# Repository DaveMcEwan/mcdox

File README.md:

mcdox - Mechanical Computer Keyboard
====================================

Layout is similar to than of the Ergodox project, but in a unibody case.

Subdirectories
--------------

- case - Lasercut design produced by exporting SVGs from KiCAD.
- doc - Documents like datasheets stored for handy reference.
- keycap - STL model generator written in OpenSCAD suitable for FDM printing.
  Generated models are tracked in `keycap/stl` because it takes a while (~10
  minutes) to generate them.
- pcb/ctrl - TODO Breakout PCB for connecting controller to switch grids.
- pcb/hand - Reversible PCB which connects the switches in a grid.
  - 38 buttons distributed over 5 rows, 8 columns.
  - Lengths beside mounting holes (6mm, 15mm, 25mm) are for standoffs to
    achieve a tenting.
  - Connect to control board with 15 core, 1mm pitch FFC-FPC cable.
    <https://www.te.com/usa-en/product-1-84953-5.html>
    <https://www.digikey.com/en/products/detail/te-connectivity-amp-connectors/1-84953-5/2567541>
    <https://uk.farnell.com/amp-te-connectivity/1-84953-5/connector-ffc-fpc-15pos-1rows/dp/3398659>
    <https://uk.farnell.com/multicomp-pro/mp-ffca10150503a/ffc-cord-15p-same-side-50mm-wht/dp/3385337>
    <https://uk.farnell.com/multicomp-pro/mp-ffca10151003a/ffc-cord-15p-same-side-100mm-wht/dp/3385339>
  - Low level lighting with LED on top and/or bottom, depending how the case
    looks.
  - All diodes (1N4148 compatible), LEDs, and resistors are 0603 (imperial).
- release - Stuff that's actually been manufactured.

BOM
---

- Keycaps - The functionally simplest parts which are also the most difficult to
  source.
  18x 1.5u, 56x 1u
- Case - Standard 3mm acrylic from laser cutter.
- PCBs - 1.2mm FR4, 2-layer, 0.15mm width/clearance
  2x mcdoxHand, 1x mcdoxCtrl
- Switches - CherryMX, or compatible like Gateron, Kailh.
  74x
- Diodes - 1 per switch.
  74x
- Microcontroller - Arduino Pro Micro from Sparkfun, or clone.
- FPC connectors
  4x
- FPC cables - Connect hand PCBs to central controller.
- LEDs - 0603 footprint
  2x
- Resistors - For LEDs and switch matrix.
  10x 220R 0603
- Pushbutton - For putting Arduino Pro Micro into programming mode.
  1x

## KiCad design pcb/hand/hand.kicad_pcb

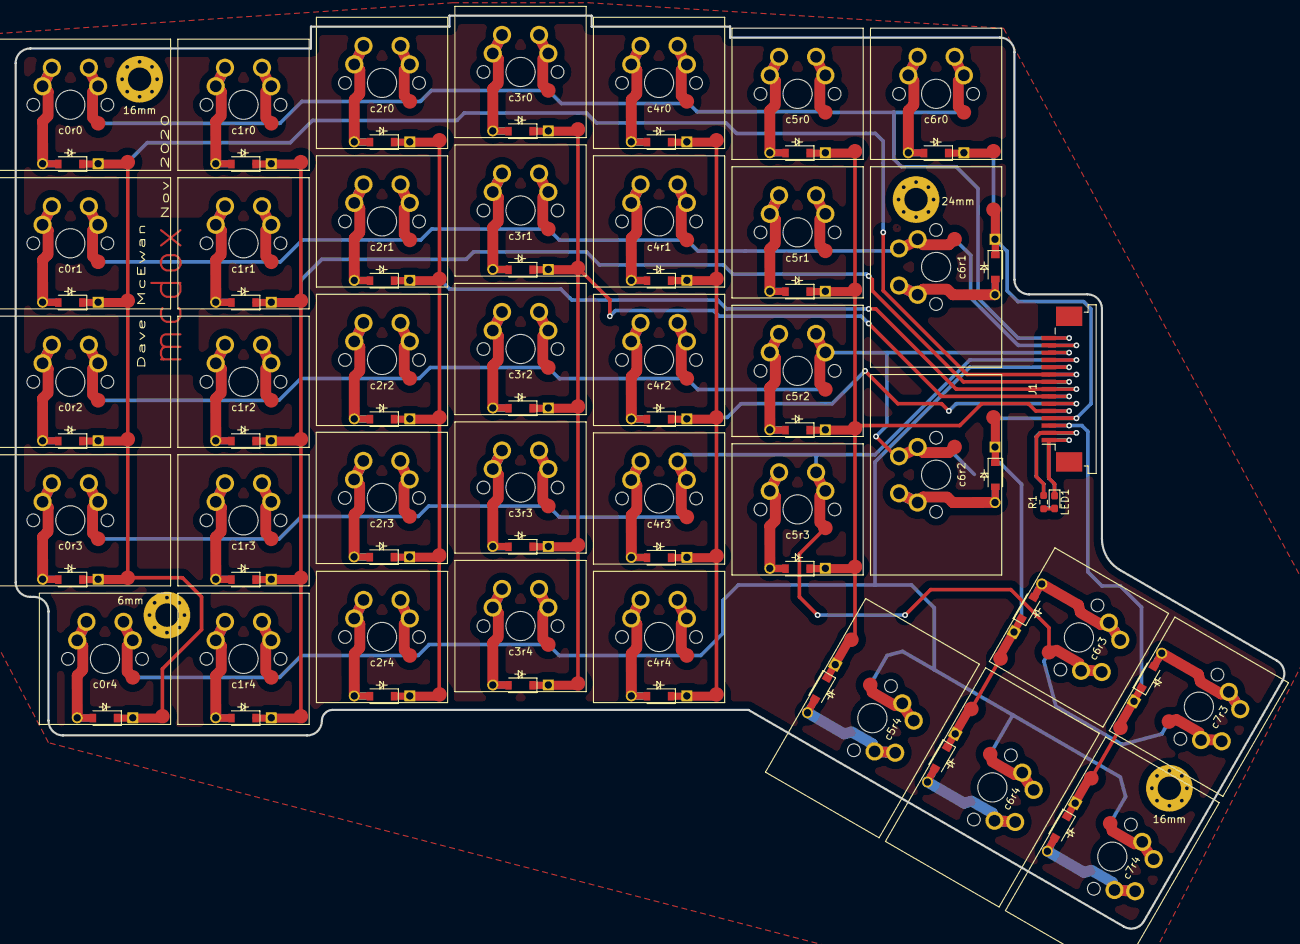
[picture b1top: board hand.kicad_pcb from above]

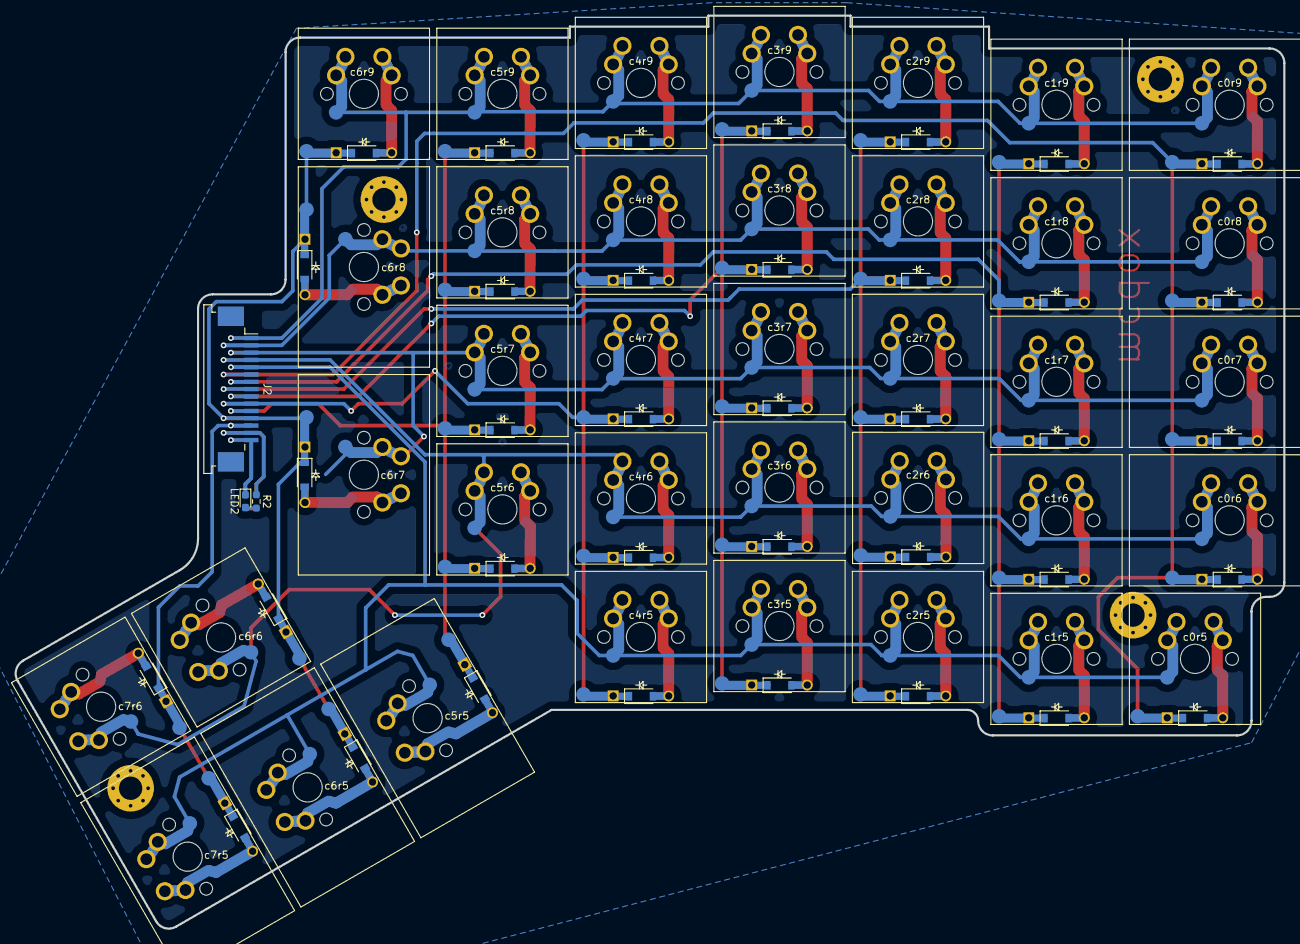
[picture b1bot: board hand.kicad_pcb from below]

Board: 2 copper layers, 174.0 x 125.2 mm, 47 parts (6 on the bottom side), 17 nets.

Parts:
6mm, 16mm, 16mm#2, 24mm: MountingHole_3.2mm_M3_Pad_Via
J1, J2: Conn_01x15; TE_1-84953-5_1x15-1MP_P1.0mm_Horizontal
LED1, LED2: LED; D_0603_1608Metric_Pad1.05x0.95mm_HandSolder
R1, R2: 100; R_0603_1608Metric_Pad0.98x0.95mm_HandSolder
c0r0, c0r1, c0r2, c0r3, c5r4, c6r1, c6r2, c6r4, c7r4: switchDiode; reversibleMX_15u
c0r4, c1r0, c1r1, c1r2, c1r3, c1r4, c2r0, c2r1, c2r2, c2r3, c2r4, c3r0, c3r1, c3r2, c3r3, c3r4, c4r0, c4r1, c4r2, c4r3, c4r4, c5r0, c5r1, c5r2, c5r3, c6r0, c6r3, c7r3: switchDiode; reversibleMX_10u

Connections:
+3V3: J1.2, J2.14, R1.1, R2.1
GND: J1.1, J2.15, LED1.1, LED2.1
unnamed: LED1.2, R1.2
unnamed: LED2.2, R2.2
col0: J1.10, J2.6, c0r0.2, c0r1.2, c0r2.2, c0r3.2, c0r4.2
col1: J1.9, J2.7, c1r0.2, c1r1.2, c1r2.2, c1r3.2, c1r4.2
col2: J1.8, J2.8, c2r0.2, c2r1.2, c2r2.2, c2r3.2, c2r4.2
col3: J1.7, J2.9, c3r0.2, c3r1.2, c3r2.2, c3r3.2, c3r4.2
col4: J1.6, J2.10, c4r0.2, c4r1.2, c4r2.2, c4r3.2, c4r4.2
col5: J1.5, J2.11, c5r0.2, c5r1.2, c5r2.2, c5r3.2, c5r4.2
col6: J1.4, J2.12, c6r0.2, c6r1.2, c6r2.2, c6r3.2, c6r4.2
col7: J1.3, J2.13, c7r3.2, c7r4.2
row0: J1.15, J2.1, c0r0.1, c1r0.1, c2r0.1, c3r0.1, c4r0.1, c5r0.1, c6r0.1
row1: J1.14, J2.2, c0r1.1, c1r1.1, c2r1.1, c3r1.1, c4r1.1, c5r1.1, c6r1.1
row2: J1.13, J2.3, c0r2.1, c1r2.1, c2r2.1, c3r2.1, c4r2.1, c5r2.1, c6r2.1
row3: J1.12, J2.4, c0r3.1, c1r3.1, c2r3.1, c3r3.1, c4r3.1, c5r3.1, c6r3.1, c7r3.1
row4: J1.11, J2.5, c0r4.1, c1r4.1, c2r4.1, c3r4.1, c4r4.1, c5r4.1, c6r4.1, c7r4.1

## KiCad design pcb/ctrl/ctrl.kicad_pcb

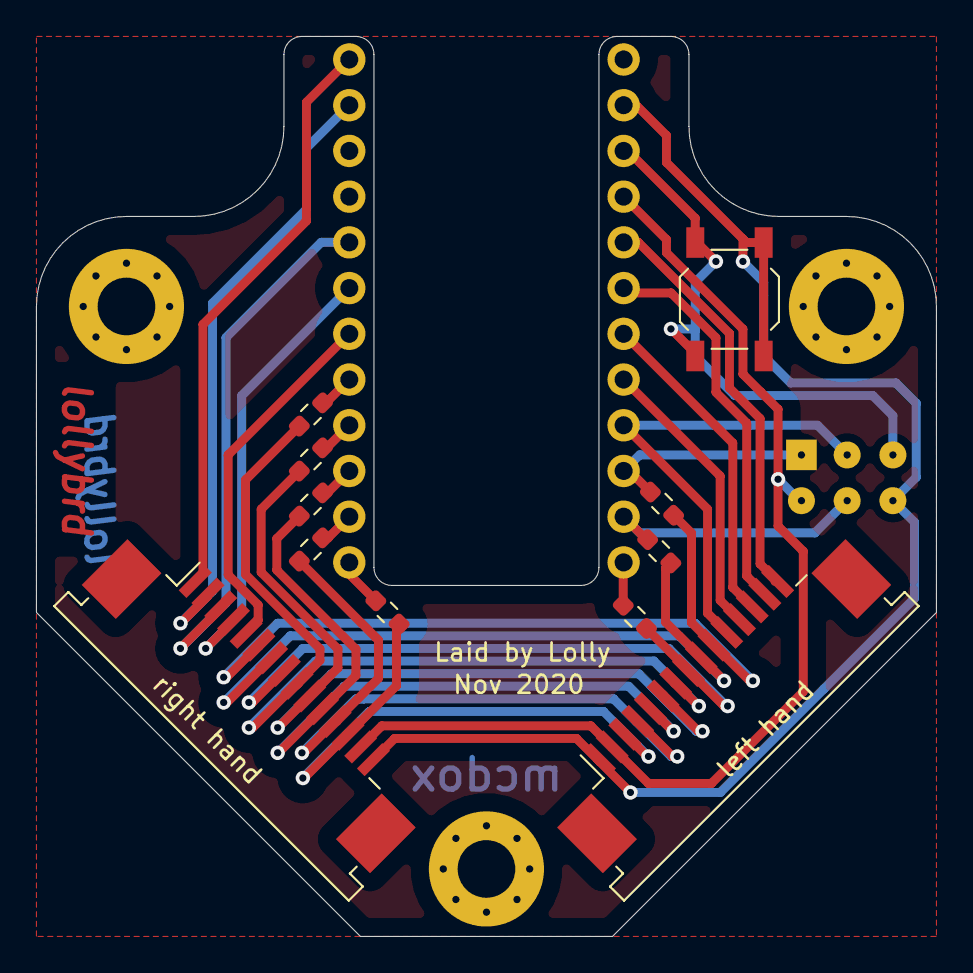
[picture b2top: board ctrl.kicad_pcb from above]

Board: 2 copper layers, 50.0 x 50.0 mm, 13 parts (1 on the bottom side), 29 nets.

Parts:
ICSP: Conn_02x03_Odd_Even; PinHeader_2x03_P2.54mm_Vertical
Jleft1: Conn_01x15; TE_1-84953-5_1x15-1MP_P1.0mm_Horizontal
Jright1: Conn_01x15; TE_1-84953-5_1x15-1MP_P1.0mm_Horizontal
R0, R1, R2, R3, R4, R5, R6, R7: 220; R_0603_1608Metric_Pad0.98x0.95mm_HandSolder
SW1: SW_Push; SW_SPST_TL3342
U1: ArduinoProMicro

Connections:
GND: ICSP.6, Jleft1.1, Jright1.15, SW1.2, U1.14
MISO: ICSP.1, R0.2, U1.22
MOSI: ICSP.4, R1.2, U1.23
unnamed: R2.2, U1.24
unnamed: R3.2, U1.12
unnamed: R4.2, U1.11
unnamed: R5.2, U1.10
unnamed: R6.2, U1.9
unnamed: R7.2, U1.8
RST: ICSP.5, SW1.1, U1.15
SCK: ICSP.3, Jleft1.11, U1.21
VCC: ICSP.2, Jleft1.2, Jright1.14, U1.16
col0: Jleft1.10, Jright1.6, R0.1
col1: Jleft1.9, Jright1.7, R1.1
col2: Jleft1.8, Jright1.8, R2.1
col3: Jleft1.7, Jright1.9, R7.1
col4: Jleft1.6, Jright1.10, R6.1
col5: Jleft1.5, Jright1.11, R5.1
col6: Jleft1.4, Jright1.12, R4.1
col7: Jleft1.3, Jright1.13, R3.1
row0: Jright1.1, U1.1
row1: Jright1.2, U1.2
row2: Jright1.3, U1.5
row3: Jright1.4, U1.6
row4: Jright1.5, U1.7
row6: Jleft1.12, U1.20
row7: Jleft1.13, U1.19
row8: Jleft1.14, U1.18
row9: Jleft1.15, U1.17

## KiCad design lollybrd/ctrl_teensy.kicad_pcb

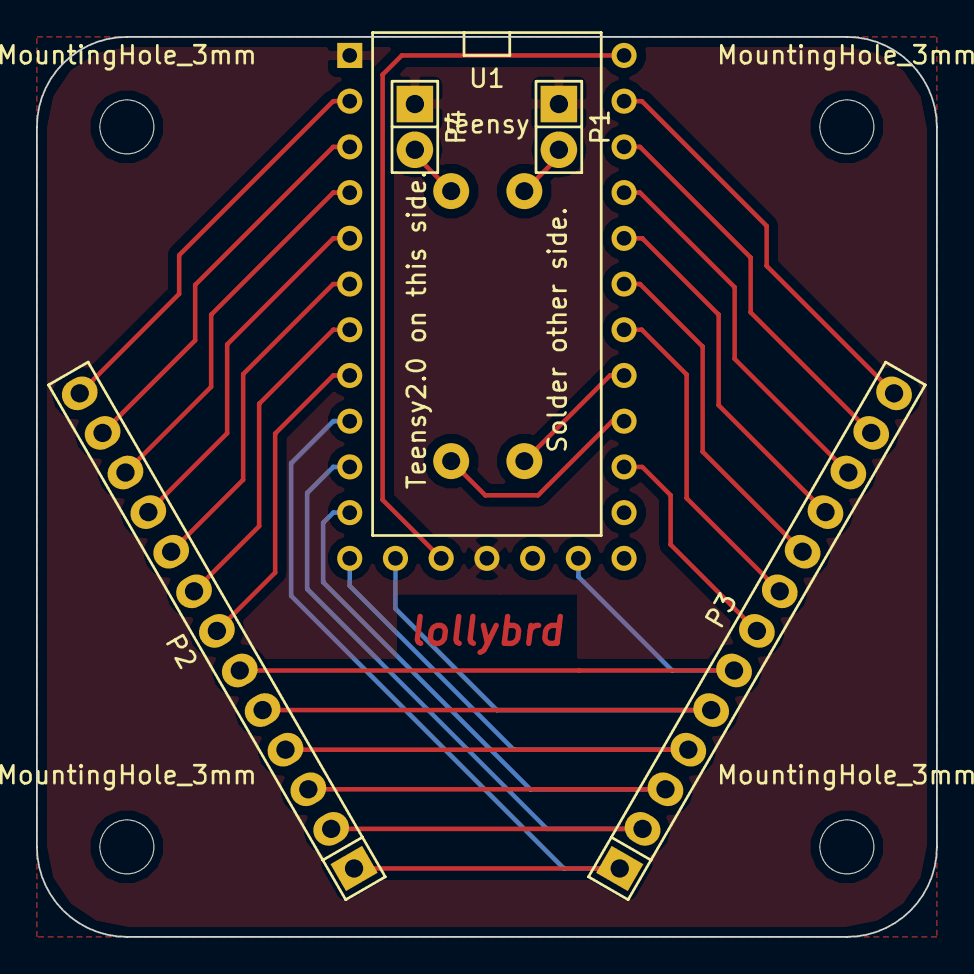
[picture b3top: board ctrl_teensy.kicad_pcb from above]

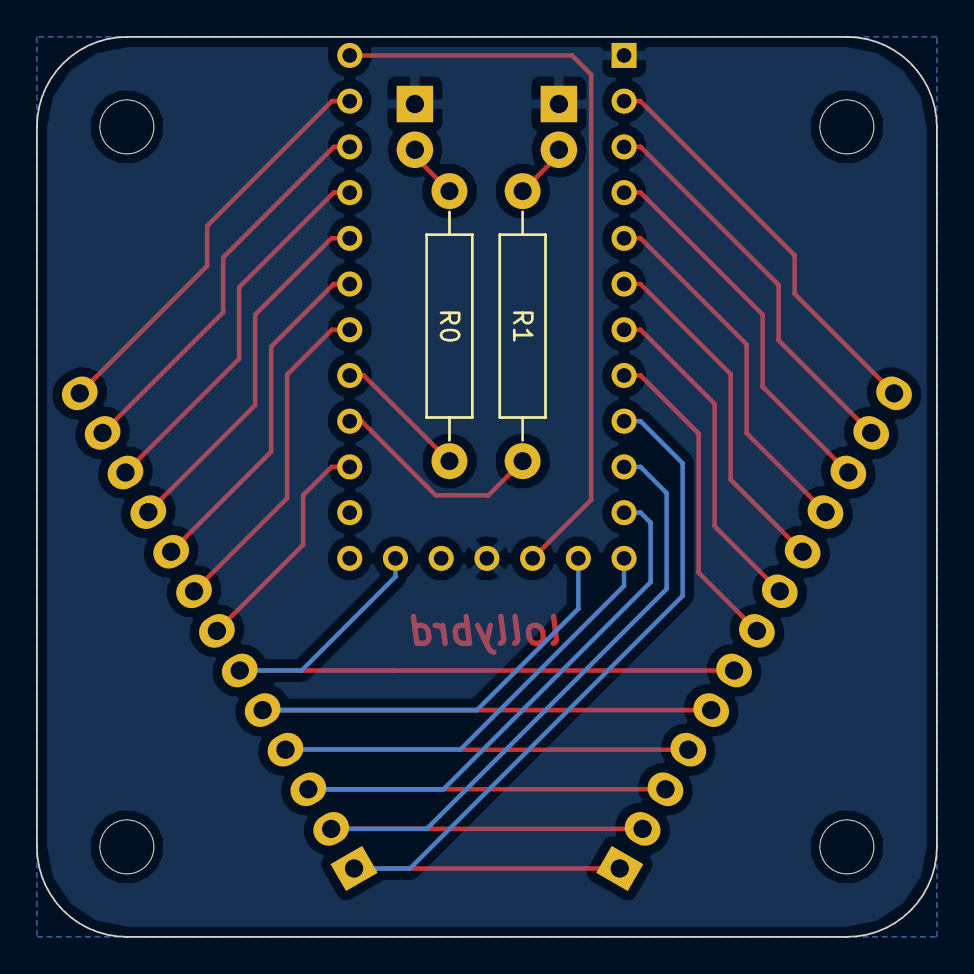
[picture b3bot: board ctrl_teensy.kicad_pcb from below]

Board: 2 copper layers, 50.0 x 50.0 mm, 11 parts (2 on the bottom side), 25 nets.

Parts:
MountingHole_3mm, MountingHole_3mm#2, MountingHole_3mm#3, MountingHole_3mm#4: VAL**; MountingHole_3mm
P1, P4: CONN_01X02; Pin_Header_Straight_1x02
P2, P3: CONN_01X13; Pin_Header_Straight_1x13
R0, R1: 220R; Resistor_Horizontal_RM15mm
U1: teensy; teensy_2.0

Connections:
GND: P1.1, P4.1, U1.GND
unnamed: R0.2, U1.B6
unnamed: R1.2, U1.B5
col0: P2.6, P3.6, U1.D4
col1: P2.5, P3.5, U1.D5
col2: P2.4, P3.4, U1.C7
col3: P2.3, P3.3, U1.C6
col4: P2.2, P3.2, U1.D3
col5: P2.1, P3.1, U1.D2
led0: P1.2, R0.1
led1: P4.2, R1.1
row0: P3.7, U1.B4
row1: P3.8, U1.F7
row2: P3.9, U1.F6
row3: P3.10, U1.F5
row4: P3.11, U1.F4
row5: P3.12, U1.F1
row6: P3.13, U1.F0
row7: P2.13, U1.B0
row8: P2.12, U1.B1
row9: P2.11, U1.B2
rowA: P2.10, U1.B3
rowB: P2.9, U1.B7
rowC: P2.8, U1.D0
rowD: P2.7, U1.D1

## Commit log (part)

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2014-11-02 Initial commit of case.
    Python generated DXF files intended to be laser cut from acrylic/stainless
    steel.
2014-11-03 Added dimensions test file.
2014-11-03 Checkin pre-generated files for convenience.
2014-11-04 Use ndim from PyPI to make it easier to get and run from github.
2014-11-05 Initial add of PCB project with only test PCB to prove out the footprints and routing method.
2014-11-11 Add gitignore.
2014-11-16 Put DXF generated DXF files in their own directory.
2014-11-16 Generate per layer DXFs to for laser cutters.
2014-11-19 Reduce trace width to 0.25mm for easier routing and move ref on silkscreen.
2014-11-19 Add header and silkscreen refs.
2014-11-22 Initial fully routed layout.
    Entirely done with DRC turned off as the alpsmx footprint doesn't comply.
    Therefore I'll really need to get one made to test if it all works.
    All the footprints were placed using the mcdox_kicad.py script.
2014-11-22 Modify base layers to make space for final PCB outline.
    Since the PCB is cut with a 0.8mm mill, and the base layers with a ~0.3mm
    laser, there should be ~0.55mm clearance all round.
2014-11-27 Footprint updates to make routing easier with thicker tracks.
    Correct diode direction marked with square pads.
    Add diode symbols to silkscreen.
    Increased foootprint track width to 0.5mm to make DIY etching easier.
2014-12-01 Footprint update after getting first run of test boards.
    Increased length of all rect smd pads to make solderign easier.
    Moved reference and name to corner for better printing.
    Joining pads on B.Cu now have solder mask on correct side.
    LED square cutout now drawn at full size for fill milling since that's
    what Seeed seem to do. As opposed to follow milling.
2014-12-02 Slightly reduced oval drill length to make soldering easier.
    Turns out that neither switch type used the full length.
2014-12-04 Add mounting hole module.
2014-12-04 Add references to silkscreen and reduce width of edge cut to 0.1
2014-12-04 First proper attempt at a full routing.
2014-12-04 Nicer reference/value for pin header in generation with mcdox_kicad.py
2014-12-04 Add gerber files for first run.
2014-12-04 Give 0.5mm margic round PCB to account for edge cuts changing size in PCB.
    The holes under switches were done with a fill-in rather than follow so
    I'm assuming the edge will be the same.
2014-12-07 Corrected pinout on schematic to match PCB.
2014-12-16 Initial add of keycap SCAD model.
    Refactored and modified from http://www.thingiverse.com/thing:468651
    Still to add stems for Matias/ALPS.
2014-12-16 Added ALPS stem support and some minor tidy.
2014-12-16 Add simple script to generate STLs for all the combinations.
    Primarily to make downloading from github easier.
    Not finished yet as I need to get to bed.
2014-12-18 Update hole sizes after getting test cut on 3mm while acrylic.
2014-12-19 Fix script to render all the different configuratons of keycap STL files.
2014-12-19 Assorted keycap scad updates.
    Added supports for very high caps.
    Some refactoring to tidy.
2014-12-19 Put line type to unix. Not sure how it managed to get bad.
2014-12-19 STL generator updates to not make everything since it takes ages.
2014-12-19 Add generated ALPS/DSA keycap STL files.
2014-12-19 Update 3 and 5 layers diagram with correct heights.
2014-12-19 Add CherryMX/DSA STLs.
2014-12-19 Add 3mm and 5mm generation to case DXFs.
2014-12-19 Generate Matias/ALPS case by default as that's the first one I'll do.
2014-12-19 Add ready-to-go zip files for both alps and cherrymx cases.
2014-12-22 Add DXF generator for laser cut keycaps for Matias switches.
2014-12-22 Initial add of Teensy2.0 breakout controller board.
2014-12-26 Updates for ALPS laser cut caps.
    Added DXF for jig and packing cardboard.
    Modified measurements to compensate for laser kerf.
2014-12-26 Added option to generate multiple stem trees.
2014-12-26 Label fixes.
2014-12-26 Remove erronous file
2014-12-29 Make PCB spacer 10mm.
    They don't *have* to be 10mm diameter but it makes the PCB mounting holes
    nicely inset and is an easy to remember size.
2014-12-29 Add gerber files for lollybrd.
2014-12-29 Rename ctrl_teensy stage 1.
2014-12-29 Removed ZIP collections as this is likely to cause confusion.
2014-12-30 Corrected pcb profiling in base cutouts.
2014-12-30 Define cap size by switch number.
2014-12-30 Add option to cut caps from the same piece of plastic as the top layer.
    This saves on material but only works if a 2 or 3mm top layer is used.
2014-12-31 Parameter for PCB profiling space in base layers.
2014-12-31 Tweak dimensions after chat with Nate.
    These are the ones sent for a test run.
2015-01-01 Tweaked case design to use 1.5x instead of 2.0x caps in the thumb cluster.
    This means there are less different parts and that those caps will wiggle
    less.
    They're still in the same position.
    PCB will need some tweaking for the one switch that has moved.
2015-01-04 Make room for IDC connector on PCB in base layers of case.
2015-01-24 Massive changes to shape.
    Realised that the two-circles shape won't fit on a 600x400 sheet so needed
    to trim it down a bit.
    While doing that a neater way specifying the paths is used which makes it
    easier to read.
    Changed default thicknesses to 3 and 5 since they are the standard.
2015-01-24 Rename top2 to 3mm.
2015-01-26 Update keycap dimensions after 1st sneaky proto run.
2015-01-28 Initial add of SVG generation.
    This should allow post-processing in Inkscape, and better compatibility
    with Lasersaur.
    Depends on latest commits to dev repo of ndim.
    Still lots to finish but MNT layer seems to be working.
2015-01-28 Add generated SVG for convenience.
2015-01-29 SVG generation for all layers.
    Still no all-in-one generation for mcdox_all.svg but viewing is so much
    easier with SVG as you can flick through images with a standard image viewer.
2015-01-30 Add generated SVG dimension test.
2015-01-30 Changes for 1st example of full pack.
2015-01-30 Add laid out cuts for 600x400mm from Hindleys.
2015-01-30 Remove unsupported matplotlib generator.
2015-02-04 Add labels to keycaps.
    top2 SVG file is hand finished in Inkscape.
2015-02-07 More labels for dvorak.
2015-02-07 Reduce hand_sep by 2mm to make alignment on laser cutting table easier.
2015-02-07 Receiver hole changes for v0.2
    v0.1 receiver holes were just a tad too thin for the stems to fit in.
2015-02-07 Make label system a bit more maintainable. UNFINISHED.
2015-02-08 Left hand label adjustments.
2015-02-09 Finish off labels for Dvorak.
2015-02-09 Add Qwerty labels.
2015-02-10 Regenerate DXFs.
2015-02-11 Initial add of ambrd.
    For now it's only a clone of a Teensy2.0 with a programming header.
    Still to add LED drivers (maybe MAX7313?) and wire up IDC connectors.
2015-02-19 Add dimensions test for stem holes as these seem to be problematic.
2015-02-24 Comment in recv size.
2015-03-06 Use new footprints in fp-lib-dmcewan
2015-03-06 Initial add of PCB.
2015-03-06 Add my library for MAX7313 symbol.
2015-03-09 Move values on MAX7313 to look like the uC.
2015-03-12 Split 26 pin 2x13 into separate 1x13 header rows to make changing orientation easier.
2015-03-19 Enlarge stem recv hole by 0.1mm to account for bad tolerences in 2mm acrylic. Also make the stem 0.1mm smaller for easier for in switch.
2015-03-20 Annotate ambrd schematic.
2015-03-20 Keycaps regen after dimension updates.
2015-06-30 Remove dodgy derived files, generate both alps and cherrymx mnt plates.
2015-07-05 Fix hole diameter needs to be just a little bigger to allow screws to insert easily.
2015-07-05 Fix holes 2.9 to 3.3mm.
2016-05-27 Initial add of v1.0 release.
2016-05-31 Remove dead whitespace.
2016-05-31 Enlarge Teensy cutout to allow for Bluefruit Feather Bluetooth LE.
2016-06-05 Remove more dead whitespace.
2016-06-06 ctrlmnt cutout.
2016-06-06 Slightly move fixing holes to work nicer with smallthumb.
2016-06-07 Add diagram for ambrd layerstack.
2016-06-12 Revert "Add misc_holes for securing battery cells."
    This reverts commit 31d76a2599f51ea8be9e0675ba8927fad5602f19.
2016-06-12 Better layerstack diagram now with battery holder.
2016-06-12 Remove old-name layerstack diagram.
    New layers are actually 1.5mm for Cherry switches to grip.
    Missed due to filesystem weirdness.
2016-06-12 Change the middle cutout of mnt to profile the PCBs in order to make space for battery.
2016-06-12 Thicken the profile for midmnt to prevent 1.5mm acrylic snapping on switch insertion.
2016-06-12 Disable dim_test generation for now.
2016-06-12 Remove redundant parameter.
2016-06-15 Major rationalisation with regular variable names.
    This has been a long time coming.
2016-06-22 Rename dodgy variable name.
2016-06-22 Correct layer names in layerstack diagram.
2016-06-22 Fairly large refactoring for coords and svg generation.
    Still not completed.
2016-06-22 Increase page size of generated SVGs for easier debug viewing.
2016-06-24 Finish refactoring/tidying.
2016-06-24 Shift everything onto 400x200 page manually.
2016-06-24 Enlarge midmnt cutout offset around sw holes.
2016-06-24 Initial add of cutout and mounting holes for AAA battery pack.
2017-05-06 Add MIT LICENSE.
2020-11-14 keycap Simplify and update for Python3.
2020-11-14 rm keycap DXF generator for ALPS.
    These keycaps are okay for a single switch, but totally naff for a whole keyboard.
2020-11-14 layerstack_ambrd -> layerstack_future
2020-11-15 pcb/hand Move testpoint pads for easier routing.
2020-11-15 pcb/hand Partial workaround for issue with copper graphics in footprint. WIP
2020-11-15 hand/pcb Routing complete and proper NPTH holes without mask.
2020-11-15 pcb/hand Mounting holes for standoff tenting.
2020-11-15 pcb/hand Convenience PNG renders.
2020-11-15 pcb/hand Convenience PDF schematic.
2020-11-15 pcb/hand Remove extra layer of hierarchy.
2020-11-18 case/layerstack Initial "palette" of configurations.
2020-11-18 case/layerstack
2020-11-18 case/layerstack All 3mm with sketches for cutouts.
    Avoid big flappy sections like on 1.0.
2020-11-18 case/mockup Beginning of mockup/practise to try some ideas.
2020-11-19 pcb/hand SOD123 diodes
2020-11-19 pcb/hand.sch Remove one key and rewire thumb cluster
2020-11-19 pcb/hand Thumb cluster rewired but not connected to rest of hand.
    checkpoint
2020-11-19 pcb/hand Mounting holes and archive footprints.
2020-11-19 pcb/hand Schematic use local footprint library.
2020-11-19 pcb/hand Refill
2020-11-19 pcb/hand Convenience render
2020-11-19 pcb/hand Vanity features on one side only to save space.
    Max dimensions 174x125.5mm
2020-11-20 pcb/ctrl Init with basic outline shape
2020-11-21 pcb/hand Label c*r* on both sides
2020-11-21 pcb/ctrl Pushbutton for bootloader programming, and backup ICSP pogo header.
2020-11-23 pdb/ctrl Positions ready for Lolly.
2020-11-28 layerstack Correct height of FFC connectors
2020-11-28 case.svg import and layerize
2020-11-28 case.svg profile.hand, profile.keycaps
2020-11-28 case.svg profile.ctrl
2020-11-28 casePalette
2020-11-29 case.svg cut.coverTop,coverBottom,innerTop
2020-11-29 case.svg cut.*
2020-12-03 case Release for MVB hackspace lasercutting session.
2020-12-03 case Move asymmetric hole non-blocking mistake.
2020-12-03 case rm old Python used in v1.0 flow.
2020-12-03 LICENSE
2020-12-03 mv doc to top level
2020-12-03 pcb/ctrl rm unmade release
2020-12-03 pcb/ctrl Convenience renders img
2020-12-03 case.svg Simplify switch hole paths.
2020-12-03 case Release fixes after today's lasercut session.
2020-12-13 case.svg Pin hole for programming button in bottom cover.
2021-01-03 doc/LED
2021-01-04 keycap First steps toward octuple part for FDM or injection mold.
2021-01-05 keycap Matias/ALPS stem
2021-01-05 keycap Generate STLs in parallel with Makefile and CSVs
2021-01-05 keycap Replace octuple with isogrid.
2021-01-06 keycap Injection gates between pairs of keycaps
2021-01-06 keycap isogrid4 STL
2021-01-06 keycap mv gatePair.margin gatePair.overshoot
2021-01-06 keycap rm mentions of FDM brim because FDM doesn't meet acceptable tolerances.
2021-01-06 keycap Single mold impression
2021-01-06 keycap Mold halves without vents, registration pins, or ejector pin holes.
2021-01-06 keycap Registration pins.
2021-01-06 keycap Vent location, missing primary channel.
2021-01-09 keycap Vents with primary and secondary square channels.
2021-01-09 keycap Reinstate keycap models with rendered STLs.
2021-01-09 README Start BOM
2021-05-29 experimental Dvorak keymap for reduced size design.
2021-06-24 Bootloader for Sparkfun Pro Micro.
    If bootloader is broken I have a usbtiny programmer from Xinda to flash
    directly after building "Caterina" bootloader from source (with Sparkfun's modifcations).
    blinkHelloWorld.hex should be removed in future.
2021-06-26 release mcdoxNov2020
